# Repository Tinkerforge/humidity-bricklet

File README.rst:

Humidity Bricklet
=================

This repository contains the firmware source code and the hardware design
files. The documentation generator configs can be found at
https://github.com/Tinkerforge/generators

Repository Content
------------------

software/:
 * examples/: Examples for all supported languages
 * build/: Compiled files
 * src/: Source code of firmware
 * Makefile: Makefile to build project

hardware/:
 * Contains KiCad project files and additionally schematics as PDF

datasheets/:
 * Contains datasheets for sensors and complex ICs that are used

Hardware
--------

The hardware is designed with the open source EDA Suite KiCad
(http://www.kicad.org). Before you are able to open the files,
you have to install the Tinkerforge kicad-libraries
(https://github.com/Tinkerforge/kicad-libraries). You can either clone
them directly in hardware/ or clone them in a separate folder and
symlink them into hardware/
(ln -s kicad_path/kicad-libraries project_path/hardware). After that you
can open the .pro file in hardware/ with KiCad and from there view and
modify the schematics and the PCB layout.

Software
--------

If you want to do your own Brick/Bricklet firmware development we highly
recommend that you use our build environment setup script and read the
tutorial (https://www.tinkerforge.com/en/doc/Tutorials/Tutorial_Build_Environment/Tutorial.html).

To compile the C code we recommend you to install the newest GNU Arm Embedded
Toolchain (https://launchpad.net/gcc-arm-embedded/+download).
You also need to install bricklib (https://github.com/Tinkerforge/bricklib)
and brickletlib (https://github.com/Tinkerforge/brickletlib).

You can either clone it directly in software/src/ or clone it in a
separate folder and symlink it into software/src/
(ln -s bricklib_path/bricklib project_path/software/src/ and
ln -s brickletlib_path/brickletlib project_path/software/src/).
Finally make sure to have CMake installed
(http://www.cmake.org/cmake/resources/software.html).

After that you can build the firmware by invoking make in software/.
The firmware (.bin) can then be found in software/build/ and uploaded
with brickv (click button "Flashing" on start screen).

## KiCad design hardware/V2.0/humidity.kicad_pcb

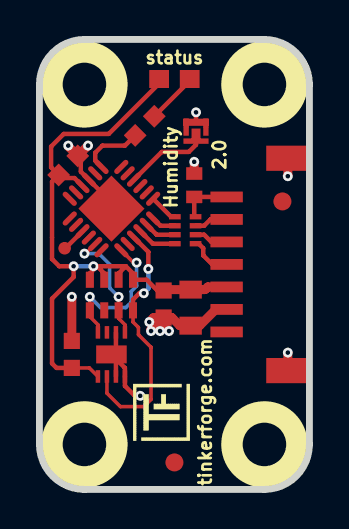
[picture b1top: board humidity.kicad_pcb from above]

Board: 2 copper layers, 15.0 x 25.0 mm, 21 parts (1 on the bottom side), 17 nets.

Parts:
C101: 10uF; C0805
C102: TBD; C0402E
C103: 1uF; C0603F
C104, C105: 100nF; C0603F
D101: blue; D0603E
Fiducial_Mark: VAL**; Fiducial_Mark
Fiducial_Mark#2: VAL**; Fiducial_Mark
P101: CON-SENSOR2
P102: BOOT; SolderJumper
P103: DEBUG; DEBUG_PAD
R101: 1k; R0603F
RP101: TBD; 4X0402
RP102: 4k7; 0603X4
U101: XMC1XXX24; QFN24-4x4mm-0.5mm
U102: SHT3x-DIS; DFN8-25x25
U103, U104, U105, U106: DRILL; DRILL_NP
VAL: CE_5mm

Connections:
GND: C101.1, C102.1, C103.1, C104.2, C105.2, P101.2, P101.EP, P102.1, U101.9, U101.EXP, U102.2, U102.7, U102.8, U102.EXP
unnamed: C102.2, P101.7, RP101.4
unnamed: D101.2, R101.2
unnamed: P101.4, RP101.1
unnamed: P101.5, RP101.2
unnamed: P101.6, RP101.3
unnamed: P102.2, U101.4
unnamed: P103.1, U101.15
unnamed: R101.1, U101.7
S-CLK: RP101.7, U101.23
S-CS: RP101.8, U101.22
S-MISO: RP101.5, U101.1
S-MOSI: RP101.6, U101.24
SCL: RP102.5, U101.19, U102.4
SDA: RP102.7, U101.17, U102.1
VCC: C101.2, C103.2, C104.1, C105.1, D101.1, P101.3, RP102.1, RP102.2, RP102.3, RP102.4, U101.10, U102.5
nRESET: RP102.8, U101.21, U102.6

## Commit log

2011-08-25 initial hardware source commit
2011-08-25 add project description
2011-09-05 Remove offset because of better optimization in newer gccs
2011-09-13 add java bindings and examples
2011-09-14 limit line length of java examples to 100 characters
2011-09-23 Add C# examples and bindings
2011-10-05 Remove Bindings and IP Connection (these are generated and they change too often) and rename bindings to examples
2011-10-05 add tinkerforge package to python imports
2011-10-06 remove faulty gcc commandline invocation
2011-10-06 add firmware version and name
2012-02-14 add compatability for different tick types
2012-02-15 Add changelog
2012-02-15 Move software changelog to software folder
2012-04-25 Unify capitalization of "IP connection" in examples
2012-05-09 Add PHP examples
2012-05-14 java: Remove unnecessary new String(...) calls
2012-05-25 Add Ruby examples
2012-06-05 Fix register_callback syntax error in Ruby examples on Windows
2012-06-12 Use correct term 'Bricklet' in example code error message
2012-06-12 Prefer IPConnection destroy over join_thread
2012-07-01 Add generate_makefile.bat for windows
2012-07-25 Add Delphi examples
2012-08-08 delphi: Add comment about UID
2012-09-07 Ignore temporary build files
2012-10-04 Extend .gitignore
2012-10-24 Make cmake find the correct objcopy binary
    On some systems cmake uses the wrong objcopy binary, tell it to use
    the correct one.
2012-11-13 Support for protocol 2.0
2012-11-28 Make python examples protocol 2.0 compatible
2012-11-29 Make Python examples compatible to Protocol V2.0 (remove destroy call)
2012-11-29 Make Ruby examples Protocol 2.0 compatible
2012-11-29 Make C examples Protocol 2.0 compatible
2012-11-29 Make Java examples Protocol 2.0 compatible
2012-11-29 Make PHP examples Protocol 2.0 compatible
2012-11-29 Make Delphi/Pascal examples Protocol 2.0 compatible
2012-11-30 delphi: Remove unnecessary parentheses and call destructor again
2012-12-05 Add protocol 2.0 compatability to C# bindings
2012-12-06 Fix C examples
2012-12-11 Avoid g++ warnings about missing casts in C examples
2013-01-09 Use specific device object for callbacks
2013-01-17 Make Java examples compatible to new listener approach
2013-01-28 Update outdated comment in Java example
2013-02-07 Use IPconnection disconnect explicitly in examples
2013-02-13 Add missing ReadKey call to C# example
2013-02-14 Fix debounce period in C# threshold example
2013-02-18 Add Visual Basic .NET examples
2013-05-15 Don't send threshold callback twice
    Fixed in brickletlib.
2013-08-09 Add shell examples
2013-08-21 windows: Don't trigger a build in generate_makefile.bat
    Also use normal make instead of a special named one.
2013-12-19 Fix wrong length for GetDebounce packet (through brickletlib)
2014-01-06 Add static assert for BrickContext size
2014-01-10 Add Perl examples
2014-01-15 php: Use const for constant values
2014-02-07 Add Mathematica examples
2014-02-10 perl: fixed namespace
2014-02-11 javascript: get/set calls inside connected callback
2014-02-11 python: typo fix in comment
2014-02-11 javascript: error message fixed
2014-02-11 javascript: short examples
2014-02-12 javascript: fixed comments
2014-02-12 perl: removed unwanted callback function
2014-02-18 javascript: examples fixed
2014-02-19 javascript: fixing comments
2014-02-19 javascript: adding html examples
2014-02-19 javascript: Fix debounce period
2014-02-20 javascript: delete Tinkerforge.js
2014-02-24 javascript: port 4280, startExample()
2014-02-28 javascript: Break long lines and cleanup whitespace
2014-03-04 Revert "python: typo fix in comment"
    There was nothing to fix, the sentence was correct already.
    This reverts commit a4ca8d8427095030b83cc6a51ed3e7e71decd77e.
2014-03-04 Fix typos
2014-03-05 Add LabVIEW examples
2014-03-06 labview: Add examples in LV2010 format
2014-03-25 matlab: add examples
2014-04-02 java: Unify constants style
2014-04-02 perl: Unify print style
2014-04-16 matlab: Unify examples and adapt to Octave callback changes
2014-04-17 matlab: Change scale value type to double
2014-04-17 matlab: Add parentheses to make pygments happy
2014-07-15 java: Replace System.console() usage with an Eclipse compatible pattern
2014-12-02 Use ReadLine instead of ReadKey for C# example
2015-02-13 vbnet: Use ReadLine instead of ReadKey
    Because ReadKey doesn't work with a pipe as stdin on the RED Brick.
2015-03-02 windows: Stop cmake from searching for mingw32-make.exe
    Using MinGW Makefiles as generator makes cmake search for mingw32-make.exe
    which might not be installed because GnuWin32's make.exe is used instead.
2015-03-26 update to latest hardware version
2015-04-09 c: Whitespace
2015-06-24 javascript: Clean up output creation
2015-07-23 Make JavaScript browser example textarea readonly
2015-07-27 Cleanup C/C++, C#, Java, Python and Ruby examples
2015-07-29 Reformat changelog
2015-07-29 Fix typo
2015-08-07 Use full device class name in Python examples
2015-08-12 Fix minor warnings in C/C++ examples
2015-08-13 Use correct simple value type
2015-08-14 Fix threshold value type in Java example
2015-08-14 Cleanup Delphi examples
2015-08-18 Cleanup VB.NET examples
2015-08-19 Cleanup Perl examples
2015-08-21 Prefer printf over puts in C/C++ examples
2015-09-09 Duplicate cmake call to fix bug during cmake creation
2015-09-30 Generator based example cleanup
2015-11-12 matlab: Fix callback handling for R2014a
    http://undocumentedmatlab.com/blog/matlab-callbacks-for-java-events-in-r2014a
2015-11-25 Include date and commit into changelog
2016-05-18 c: Add missing device destroy call
2016-07-01 Make the change UID comment more explicit
2017-04-13 csharp: Adapt example
2017-04-21 shell: Adapt example
2017-04-28 schematic for new prototype
2017-05-04 completed prototype
2017-05-04 fiducials added
2017-05-04 fix i2c routing
2017-05-04 add debug pad
2017-05-04 prototype fixed
2017-05-05 add second prototype (alternative)
2017-05-08 add description
2017-05-18 update sensor footprint
2017-06-02 octave: Use javaObject instead of deprecated java_new
2017-11-30 Update examples from generator
2017-12-07 mathematica: Also generate .nb files
2018-01-30 Update examples
2018-02-19 javascript: Close div tag correctly
2018-02-20 Cleanup KiCad libraries config
    Ensure LibDir=kicad-libraries and LibName1=tinkerforge.
    Remove special library.
2018-05-24 perl: Use strict in examples
2018-07-11 Add Makefile with docker support
2018-07-11 Remove obsolete generate_makefile scripts
2018-07-11 Update directory structure and build instructions
2018-07-18 examples: Fix typo
2018-11-06 Add rust examples
2018-11-07 rust: Accept host names for ip connection, fix naming inconsistencies
2018-11-07 rust: Rename callback receivers.
2018-12-14 Add go examples.
2018-12-14 go: Fix printf parameters.
2018-12-18 go: Change import path.
2018-12-18 go: Change import path again.
2018-12-20 rust: Reformat examples.
2019-01-24 mqtt: Add examples.
2019-01-24 mqtt: Fix example header.
2019-01-24 mqtt: Remove executable bit in example permissions.
2019-01-24 go: Minor example fixes.
2019-01-24 mqtt: Minor example fixes.
2019-03-28 mqtt: Fix whitespace.
2019-08-22 c: Adapt to bindings changes
2019-08-27 go: Escape '%' in examples.
2020-01-13 examples: Use python3 input instead of python2 raw_input.
2020-01-13 examples: mqtt: Remove trailing whitespace.
2021-10-25 Update KiCad link
    https://www.kicad.org/blog/2021/10/Avoid-links-to-former-kicad-domain/
2022-07-06 Add license files.

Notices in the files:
hardware/V2.0/humidity.kicad_pcb:
Licensed under CERN OHL v.1.1
Copyright (©) 2017, B.Nordmeyer
Copyright Tinkerforge GmbH 2017.
This documentation describes Open Hardware and is licensed under the
CERN OHL v. 1.1.
